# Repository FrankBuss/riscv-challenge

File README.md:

# MIDI synthesizer

This is the MIDI synthesizer project for the [RISC-V Design Challenge](https://www.hackster.io/contests/hackitriscv). I'm using [this board](https://lcsc.com/product-detail/Development-Boards-Kits_WCH-Jiangsu-Qin-Heng-CH32V307V-EVT-R1_C2943980.html) for it.

The board is configured to receive the MIDI data with an opto-isolator with the standard MIDI frequency of 31,250 Hz. The firmware then detects note-on and note-off events and generates a PWM signal with the requested pitch.

Soldering the MIDI-in board and testing the project:

https://www.youtube.com/watch?v=y-bby_u5XV8

## Software

First install MounRiver, as described here:
https://www.youtube.com/watch?v=JHzsH9RhTR4

Then download or clone this repository and open the project file `midi-synthesizer.wvproj` in the `midi-synthesizer` directory. You can then build and upload it.

## Hardware

Circuit diagram of the MIDI-in board:

You can find the KiCad project in the `midi-in-module` directory. There is also a `gerbers.zip` file, which you can use to order your board from a PCB manufacturer like https://jlcpcb.com.

Parts list, which you can get from https://www.digikey.com:

| Id | Designator | Package | Quantity | Designation | Digi-Key Part Number |
| -- | -- | -- | -- | -- | -- |
| 1 | D1 | SOT-23 | 1 | BAV99 | 3191-BAV99CT-ND |
| 2 | R1,R3,R4 | R_1206_3216Metric | 3 | 220 | 311-220ERCT-ND |
| 3 | J3,J2 | PinHeader_1x10_P2.54mm_Vertical | 2 | Conn_01x10_Male | Z12462-ND |
| 4 | J1 | DIN_CUI_SD-50BV | 1 | DIN-5-GND | CP-3150-ND |
| 5 | C1 | C_0805_2012Metric | 1 | 100n | 478-1395-1-ND |
| 6 | R2 | R_0805_2012Metric | 1 | 2.2k | 311-2.20KLRCT-ND |
| 7 | U1 | DIP-6_W8.89mm_SMDSocket_LongPads | 1 | H11L1 | H11L1SMCT-ND |

When soldering it, you can use (this interactive placement tool)[midi-in-module/bom/ibom.html] to find the location of the components.

You can connect the PWM output directly to a high impedance amplifier, or you can build a simple amplifier with a N-channel MOSFET to drive a speaker, as seen in the video:

## Connections

On the dev board, connect PA0 to LED1, to light the LED when a note is playing. Connections to the MIDI-in board:

| dev board | MIDI-in board |
| -- | -- |
| VCC | +5V |
| GND | GND |
| PA10 | MIDI-in |

Note: VCC is 3.3V. The MIDI-in board works with 5V and 3.3V.

Then connect PA8 to an audio amplifier, connect a MIDI keyboard, or a USB-to-MIDI interface as seen in the video.

## Credits

The MIDI demo file is from https://www.free-scores.com/download-sheet-music.php?pdf=11596#.

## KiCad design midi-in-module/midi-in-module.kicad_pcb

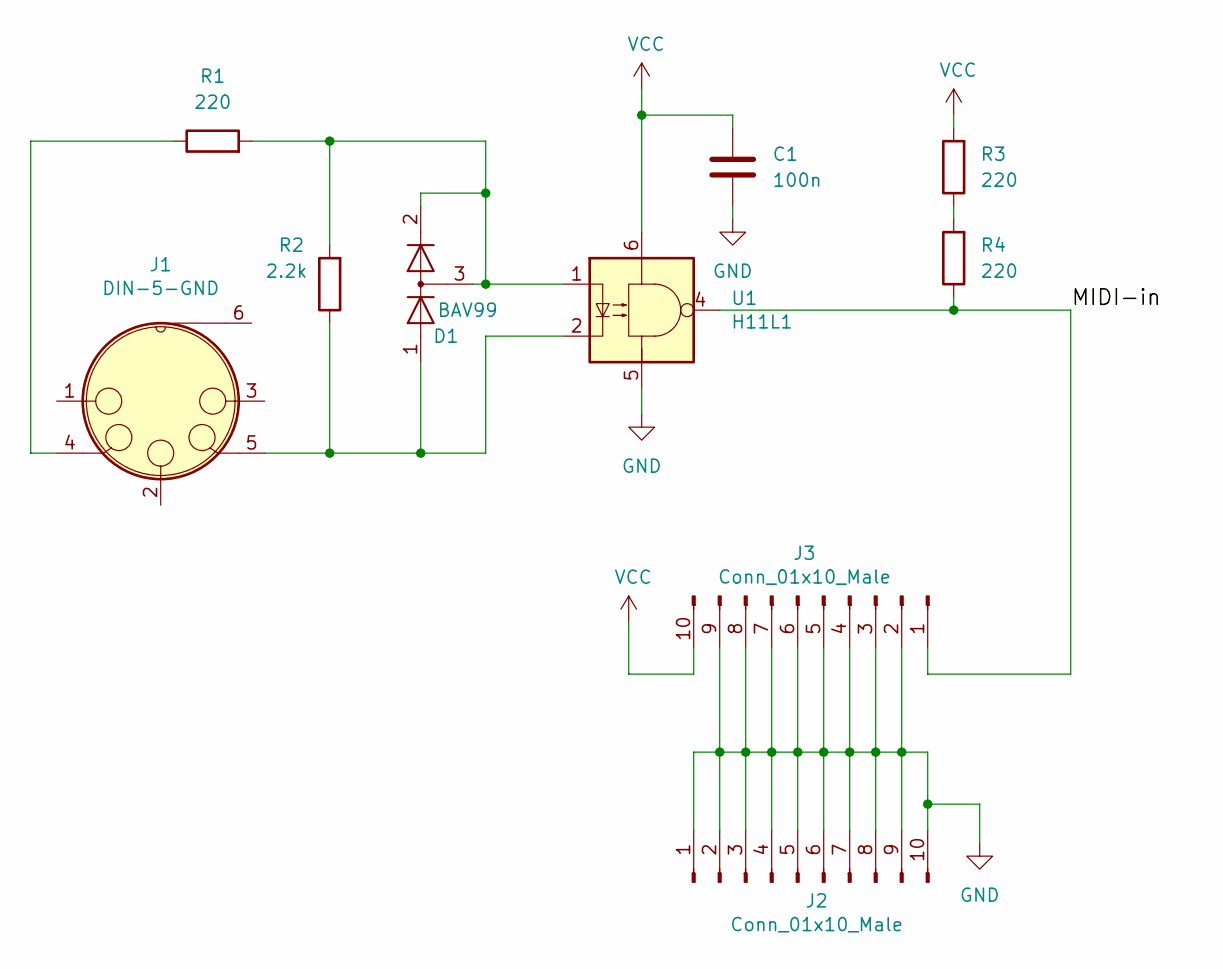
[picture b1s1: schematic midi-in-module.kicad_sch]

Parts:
C1: 100n; C_0805_2012Metric
D1: BAV99; SOT-23
J1: DIN-5-GND; DIN_CUI_SD-50BV
J2, J3: Conn_01x10_Male; PinHeader_1x10_P2.54mm_Vertical
R1, R3, R4: 220; R_1206_3216Metric
R2: 2.2k; R_0805_2012Metric
U1: H11L1; DIP-6_W8.89mm_SMDSocket_LongPads

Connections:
GND: C1.2, J2.1, J2.2, J2.3, J2.4, J2.5, J2.6, J2.7, J2.8, J2.9, J2.10, J3.2, J3.3, J3.4, J3.5, J3.6, J3.7, J3.8, J3.9, U1.5
unnamed: D1.1 (K), J1.5, R2.1, U1.2
unnamed: D1.2 (A), D1.3 (K), R1.2, R2.2, U1.1
unnamed: J1.4, R1.1
unnamed: J3.1, R4.1, U1.4
unnamed: R3.1, R4.2
VCC: C1.1, J3.10, R3.2, U1.6

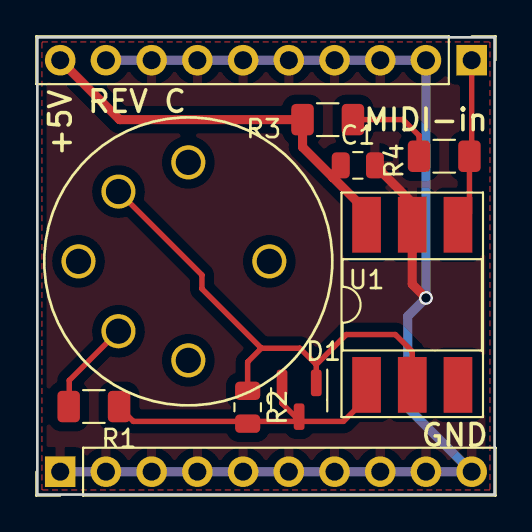
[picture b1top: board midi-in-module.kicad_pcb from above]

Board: 2 copper layers, 25.4 x 25.4 mm, 10 parts (0 on the bottom side), 7 nets.

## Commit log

2022-09-25 added documentation and the built output
2022-09-25 improved documentation
